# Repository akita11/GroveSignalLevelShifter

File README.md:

# Grove Signal Level Shifter

Grove端子の2本の信号線の信号電圧を、5V/3.3Vで相互に変換します。例えば信号電圧が3.3VのM5Stackシリーズで5V系のI2CデバイスやUART通信を行うことができます。

電源が5V、信号が3.3Vの「Groveコネクタ」（M5Stackシリーズなど）を、5V系のGroveから使用することができます。
電源は、どちらかのコネクタから+5Vを与えてください。

## 使い方

- 基板裏面「5V」と書かれたら側のGroveコネクタに5V系のGroveケーブルを接続します。
- 基板裏面「3V3」と書かれたら側のGroveコネクタに3.3V系のGroveケーブルを接続します。
  - こちら側のGroveコネクタの電源は、「5V」側のものがそのまま接続されています。3.3Vに降圧されませんので注意してください。

## Author

Junichi Akita (@akita11) / akita@ifdl.jp

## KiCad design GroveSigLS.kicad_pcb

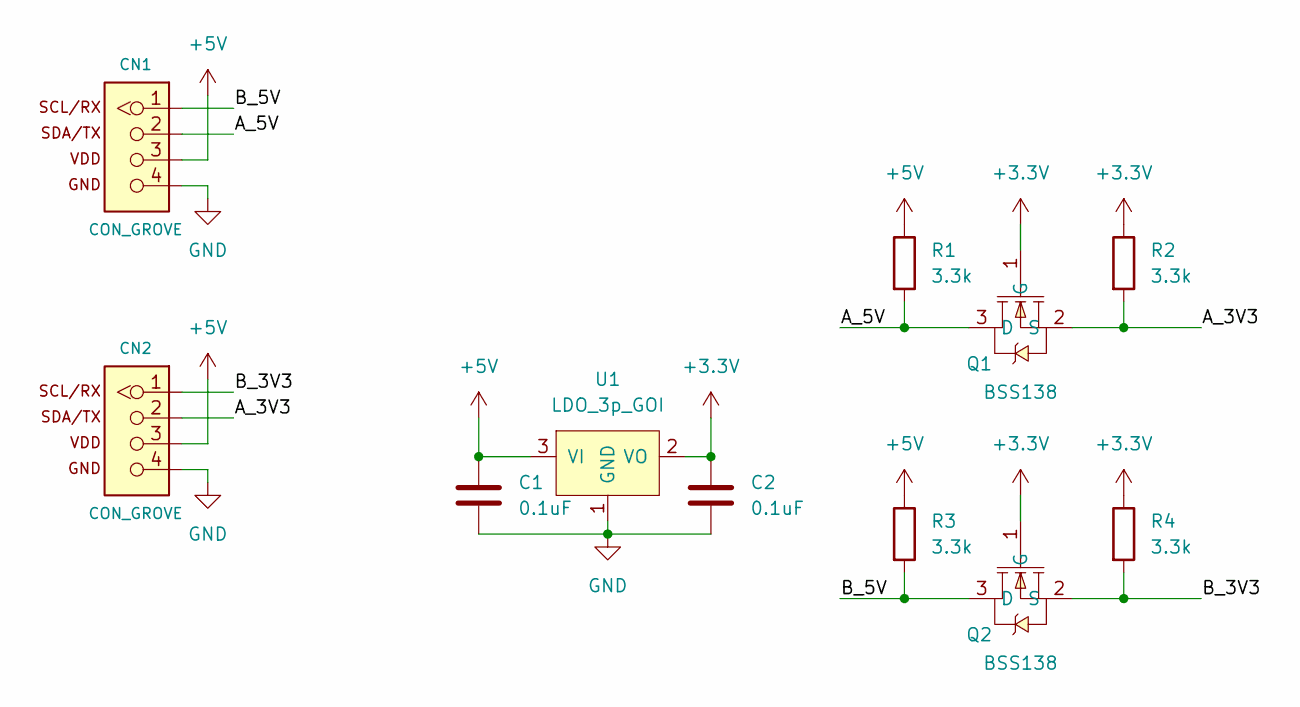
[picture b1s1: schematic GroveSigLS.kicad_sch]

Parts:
C1, C2: 0.1uF; C_0603_1608Metric; LCSC C14663
CN1, CN2: CON_GROVE; CON_GROVE_H_roundPad
Q1, Q2: BSS138; SOT-23-3_L2.9-W1.6-P1.90-LS2.8-BR; MPN BSS138; LCSC Part C2874697
R1, R2, R3, R4: 3.3k; R_0603_1608Metric; LCSC C22978
U1: LDO_3p_GOI; SOT-23; LCSC C22470928

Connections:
+3.3V: C2.1, Q1.1 (G), Q2.1 (G), R2.1, R4.1, U1.2 (VO)
+5V: C1.1, CN1.3, CN2.3, R1.1, R3.1, U1.3 (VI)
/A_3V3: CN2.2, Q1.2 (S), R2.2
/A_5V: CN1.2, Q1.3 (D), R1.2
/B_3V3: CN2.1, Q2.2 (S), R4.2
/B_5V: CN1.1, Q2.3 (D), R3.2
GND: C1.2, C2.2, CN1.4, CN2.4, U1.1 (GND)

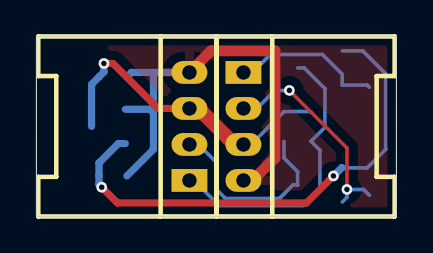
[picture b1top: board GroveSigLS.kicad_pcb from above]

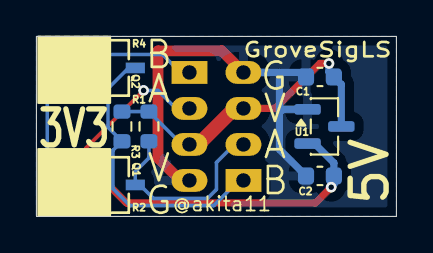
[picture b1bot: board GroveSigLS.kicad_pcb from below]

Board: 2 copper layers, 20.0 x 10.0 mm, 11 parts (9 on the bottom side), 7 nets.
